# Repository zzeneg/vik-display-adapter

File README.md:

# VIK Bare Display adapter

Small adapter for bare LCD displays to [VIK](https://github.com/sadekbaroudi/vik) connector.

## Features

- horizontal or vertical VIK connector (FPC)
- automatic reset (no separate pin)
- two mounting holes for solder nuts
- testing pads

## Supported displays

Theoretically any display with 12pin welding type FPC with this pin out:

```
- GND
- LEDK
- LEDA
- VDD
- GND
- GND
- DC
- CS
- SCL
- SDA
- RESET
- GND
```

Bare displays can be used with any PCB size, but they are pretty fragile without any support, so be careful.

Existing PCBs for specific sizes:

- 1.28" round display ([example](https://www.aliexpress.com/item/1005006051175539.html))
- universal **0.7mm** pitch / 1.47" rectangular display ([example](https://www.aliexpress.com/item/1005004833011998.html))
- universal **0.8mm** pitch ([example](https://www.aliexpress.com/item/1416043398.html))

## Forced backlight

If controlled backlight is not needed (for example no GPIO2 on VIK), GND testing pad can be bridged to R1 bottom pad, for 100% backlight. In that case S8050 and R1 parts are not needed.

## Photos

## BOM

All SMD components are 1206 size

- 10R resistor
- 100k resistor
- 1uF capacitor
- 100nF capacitor
- S8050 transistor
- 12pin FFC connector vertical/horizontal (both can be soldered in the same time)

## VIK module certification

| Category                | Classification       | Response           |
| ----------------------- | -------------------- | ------------------ |
| FPC connector           | Required             | :heavy_check_mark: |
| Breakout pins           | Recommended          | :x:                |
| Uses: SPI               | Optional             | :heavy_check_mark: |
| SPI used for SPI only   | Strongly recommended | :heavy_check_mark: |
| Uses: I2C               | Optional             | :x:                |
| I2C used for I2C only   | Strongly Recommended | N/A                |
| I2C pull ups            | Required             | N/A                |
| Uses: RGB               | Optional             | :x:                |
| Uses: Extra GPIO 1      | Optional             | :heavy_check_mark: |
| Uses: Extra GPIO 2      | Optional             | :heavy_check_mark: |
| Standard PCB Size/Mount | Strongly recommended | :x:                |

## Used projects and resources

- https://www.waveshare.net/w/upload/f/f5/1.47inch_LCD_Module_SchDoc.pdf
- https://hackaday.io/project/168130-universal-ips-display-breakout-board
- 1.47" LCD model https://grabcad.com/library/1-47-rgb-tft-lcd-screen-display-module-172-320-ips-screen-st7789-driver-8pin-1
- 1.28" round LCD model https://grabcad.com/library/1-28-lcd-ga9a01-1

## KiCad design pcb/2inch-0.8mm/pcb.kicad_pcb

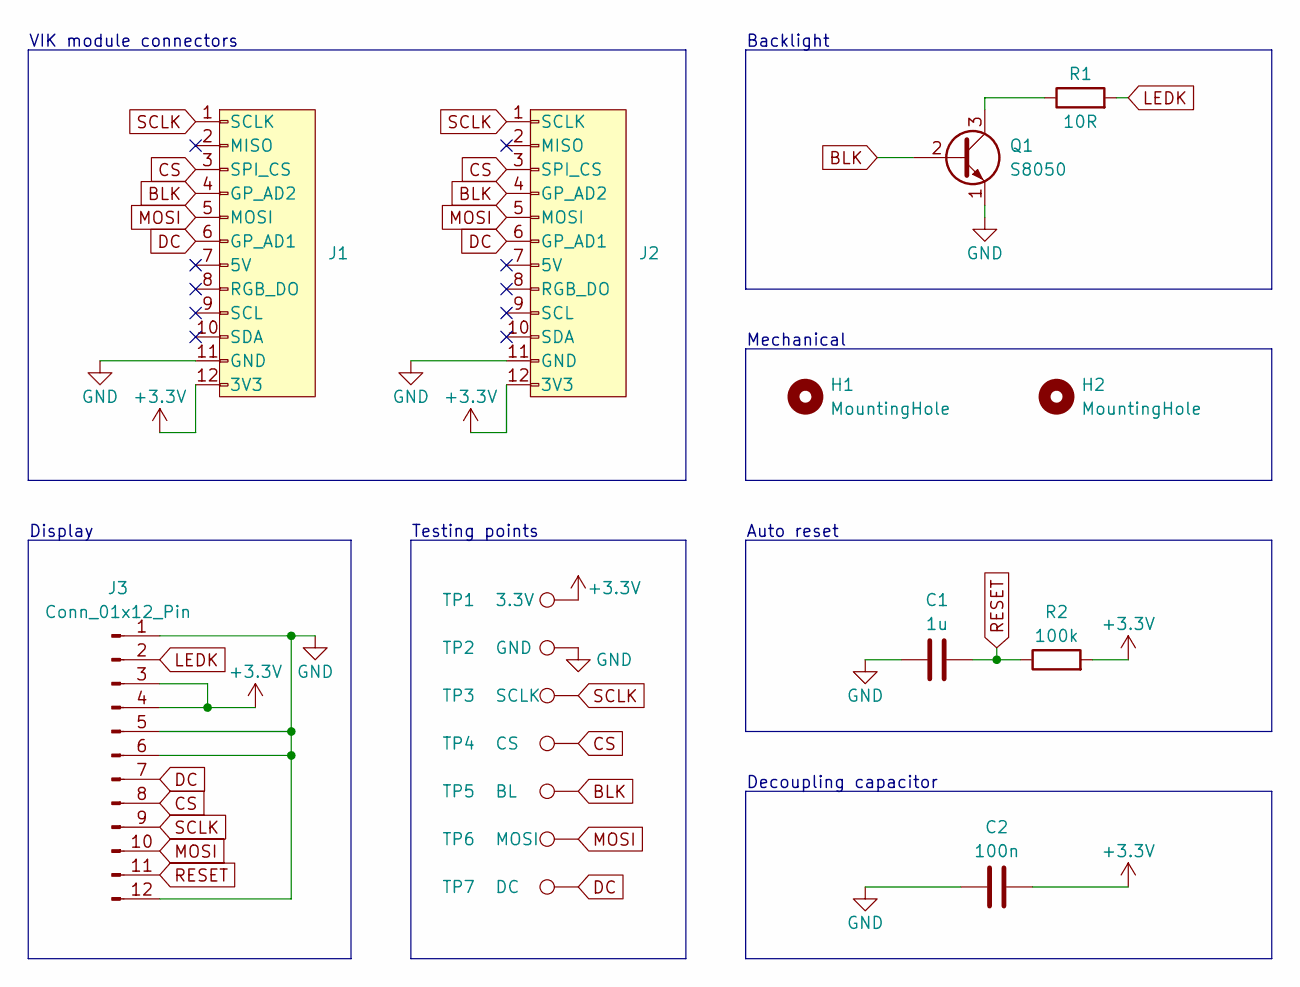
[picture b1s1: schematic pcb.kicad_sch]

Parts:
C1: 1u; C_1206_3216Metric_Pad1.33x1.80mm_HandSolder
C2: 100n; C_1206_3216Metric_Pad1.33x1.80mm_HandSolder
H1, H2: MountingHole; Hole_M2-solder-nut-2.5
J1: vik-module-connector; vik-module-connector-horizontal
J2: vik-module-connector; Connector_VIK-vertical-module
J3: Conn_01x12_Pin; Connector_Display-12pin-0.8mm
Q1: S8050; Transistor-S8050-SOT-23
R1: 10R; R_1206_3216Metric_Pad1.30x1.75mm_HandSolder
R2: 100k; R_1206_3216Metric_Pad1.30x1.75mm_HandSolder
TP1: 3.3V; TestPoint_Pad_D2.0mm
TP2: GND; TestPoint_Pad_D2.0mm
TP3: SCLK; TestPoint_Pad_D2.0mm
TP4: CS; TestPoint_Pad_D2.0mm
TP5: BL; TestPoint_Pad_D2.0mm
TP6: MOSI; TestPoint_Pad_D2.0mm
TP7: DC; TestPoint_Pad_D2.0mm

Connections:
+3.3V: C2.2, J1.12 (3V3), J2.12 (3V3), J3.3, J3.4, R2.2, TP1.1
BLK: J1.4 (GP_AD2), J2.4 (GP_AD2), Q1.2 (B), TP5.1
CS: J1.3 (SPI_CS), J2.3 (SPI_CS), J3.8, TP4.1
DC: J1.6 (GP_AD1), J2.6 (GP_AD1), J3.7, TP7.1
GND: C1.1, C2.1, J1.11 (GND), J2.11 (GND), J3.1, J3.5, J3.6, J3.12, Q1.1 (E), TP2.1
LEDK: J3.2, R1.2
MOSI: J1.5 (MOSI), J2.5 (MOSI), J3.10, TP6.1
unnamed: Q1.3 (C), R1.1
RESET: C1.2, J3.11, R2.1
SCLK: J1.1 (SCLK), J2.1 (SCLK), J3.9, TP3.1

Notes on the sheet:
Display
Mechanical
Backlight
Auto reset
Decoupling capacitor
Testing points
VIK module connectors

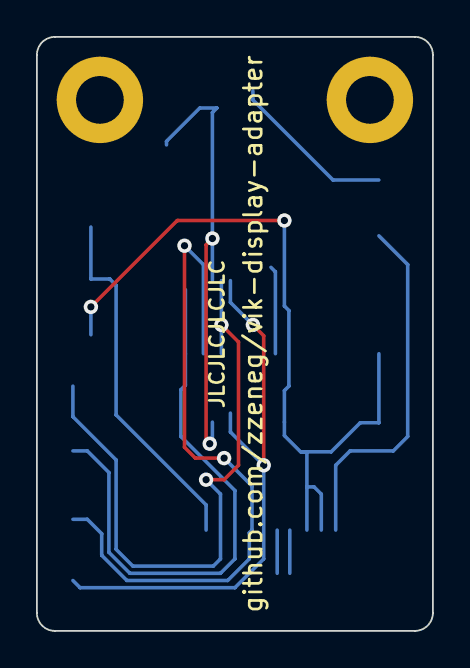
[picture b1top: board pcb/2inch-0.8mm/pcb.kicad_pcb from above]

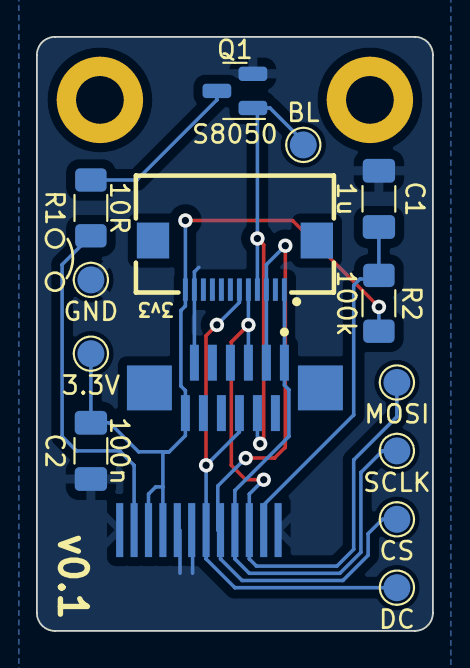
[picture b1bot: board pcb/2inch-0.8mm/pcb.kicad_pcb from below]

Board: 2 copper layers, 22.0 x 33.0 mm, 17 parts (17 on the bottom side), 10 nets.

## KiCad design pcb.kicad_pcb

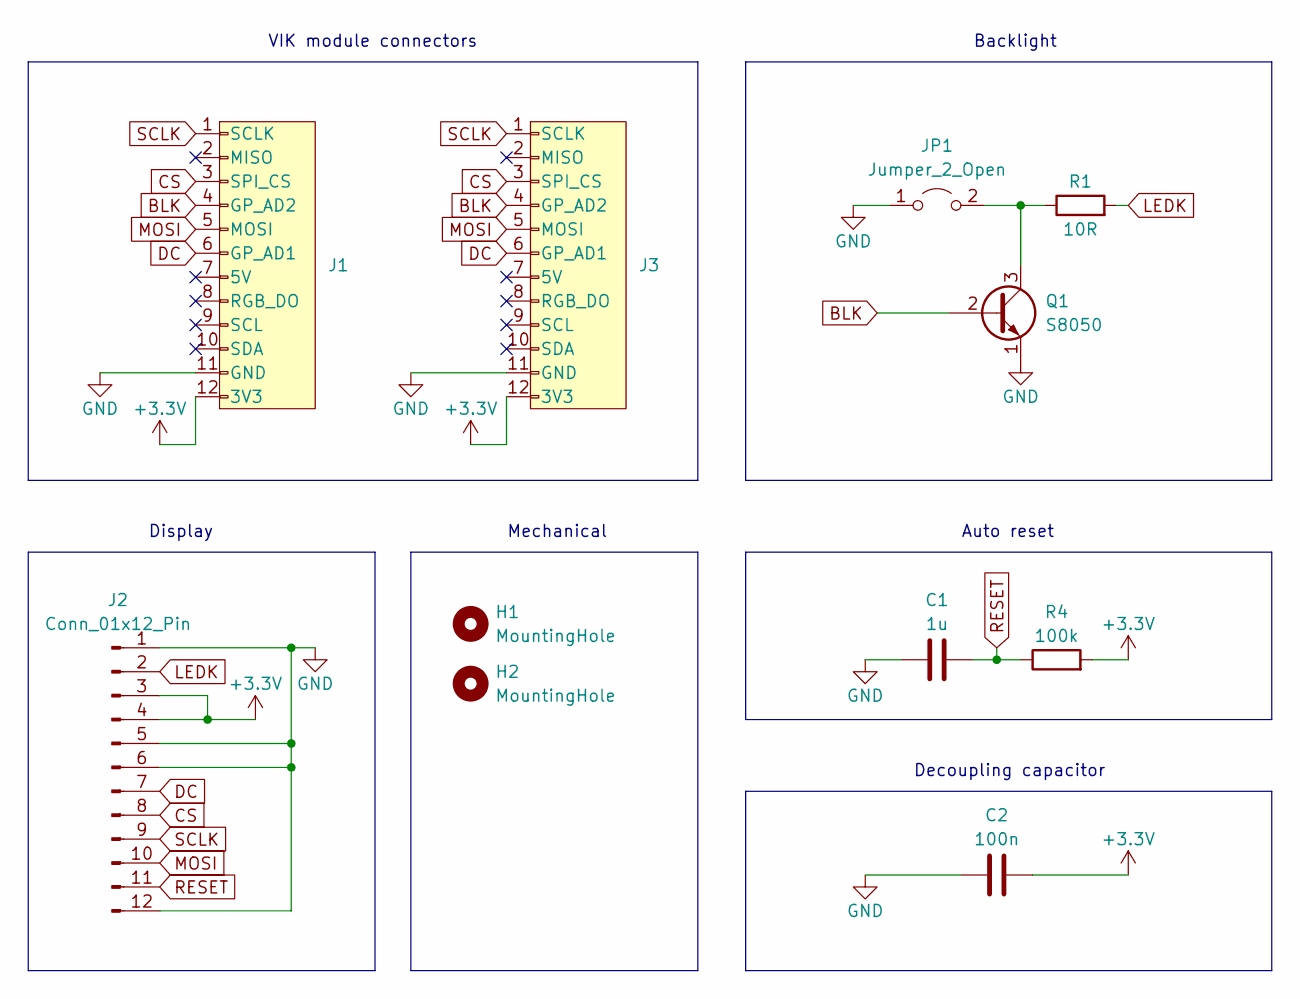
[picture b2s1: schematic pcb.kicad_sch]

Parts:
C1: 1u; C_1206_3216Metric_Pad1.33x1.80mm_HandSolder
C2: 100n; C_1206_3216Metric_Pad1.33x1.80mm_HandSolder
H1, H2: MountingHole; Hole_M2-TH
J1: vik-module-connector; vik-module-connector-horizontal
J2: Conn_01x12_Pin; fpc-0.7mm-12pin
J3: vik-module-connector; vik-module-connector-vertical
JP1: Jumper_2_Open; SolderJumper-2_P1.3mm_Open_RoundedPad1.0x1.5mm
Q1: S8050; SOT-23
R1: 10R; R_1206_3216Metric_Pad1.30x1.75mm_HandSolder
R4: 100k; R_1206_3216Metric_Pad1.30x1.75mm_HandSolder

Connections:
+3.3V: C2.2, J1.12 (3V3), J2.3, J2.4, J3.12 (3V3), R4.2
BLK: J1.4 (GP_AD2), J3.4 (GP_AD2), Q1.2 (B)
CS: J1.3 (SPI_CS), J2.8, J3.3 (SPI_CS)
DC: J1.6 (GP_AD1), J2.7, J3.6 (GP_AD1)
GND: C1.1, C2.1, J1.11 (GND), J2.1, J2.5, J2.6, J2.12, J3.11 (GND), JP1.1 (A), Q1.1 (E)
LEDK: J2.2, R1.2
MOSI: J1.5 (MOSI), J2.10, J3.5 (MOSI)
unnamed: JP1.2 (B), Q1.3 (C), R1.1
RESET: C1.2, J2.11, R4.1
SCLK: J1.1 (SCLK), J2.9, J3.1 (SCLK)

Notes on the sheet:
Display
Backlight
Auto reset
Mechanical
VIK module connectors
Decoupling capacitor

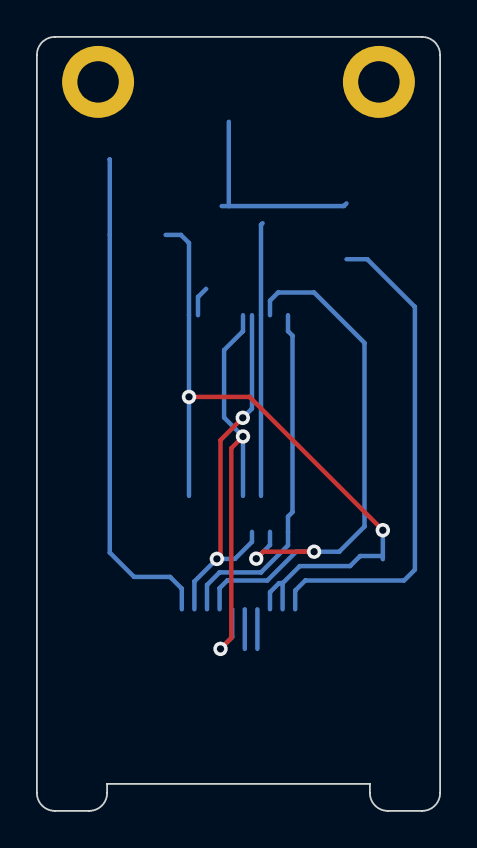
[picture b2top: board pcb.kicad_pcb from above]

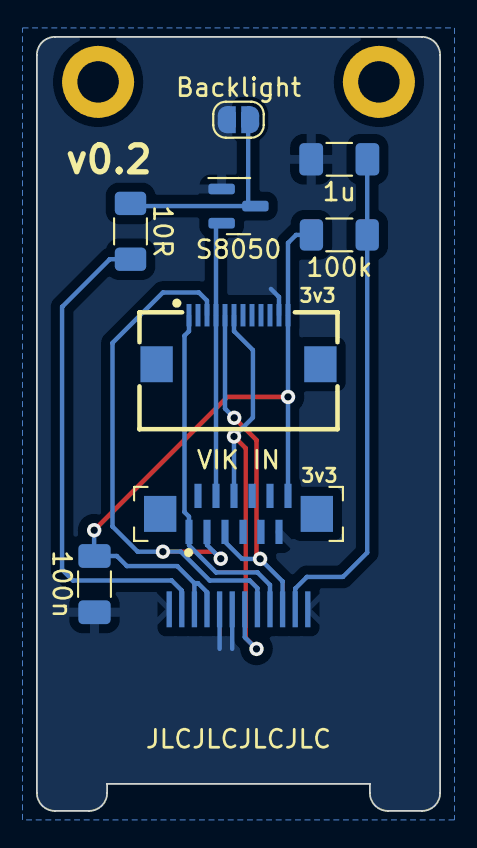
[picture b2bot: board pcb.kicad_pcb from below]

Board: 2 copper layers, 22.4 x 43.0 mm, 11 parts (9 on the bottom side), 10 nets.

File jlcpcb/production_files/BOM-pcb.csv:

Comment,Designator,Footprint,LCSC
Conn_01x12_Pin,J2,fpc-0.7mm-12pin,
MountingHole,H2,Hole_M2-TH,
MountingHole,H1,Hole_M2-TH,
1u,C1,C_1206_3216Metric_Pad1.33x1.80mm_HandSolder,
10R,R1,R_1206_3216Metric_Pad1.30x1.75mm_HandSolder,
vik-module-connector,J1,vik-module-connector-horizontal,
100n,C2,C_1206_3216Metric_Pad1.33x1.80mm_HandSolder,
vik-module-connector,J3,vik-module-connector-vertical,
Backlight,JP1,SolderJumper-2_P1.3mm_Open_RoundedPad1.0x1.5mm,
S8050,Q1,SOT-23,
100k,R4,R_1206_3216Metric_Pad1.30x1.75mm_HandSolder,

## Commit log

2024-01-14 v0.1
2024-01-14 v0.2
2024-02-03 v1.0
2024-02-03 1.28-round - v0.1
2024-02-09 2inch 0.8mm - v0.1
2024-02-25 small updates
2024-02-29 add VIK card
